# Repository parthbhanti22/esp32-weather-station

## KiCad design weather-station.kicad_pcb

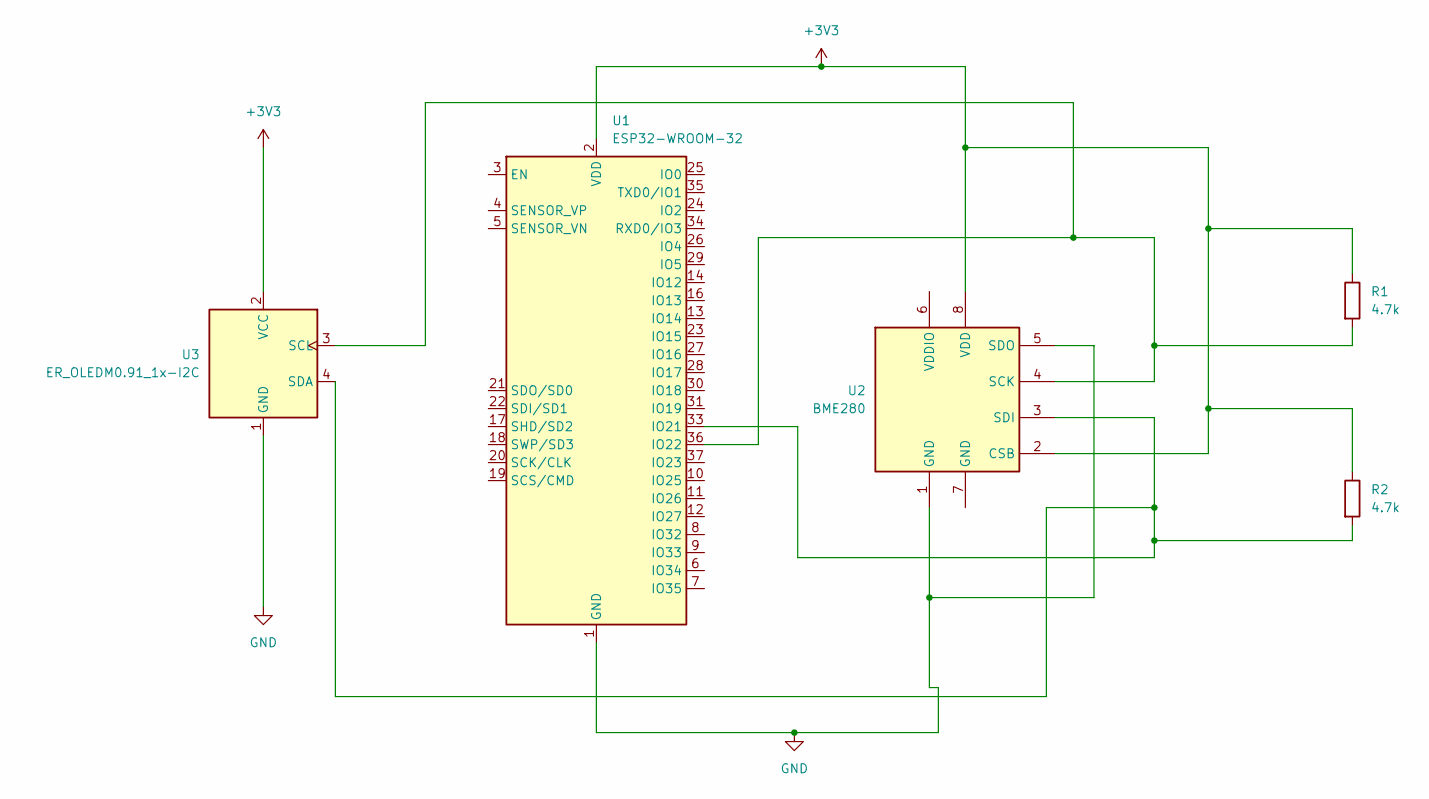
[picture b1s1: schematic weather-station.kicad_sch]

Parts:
R1, R2: 4.7k; R_1206_3216Metric_Pad1.30x1.75mm_HandSolder
U1: ESP32-WROOM-32
U2: BME280; Bosch_LGA-8_2.5x2.5mm_P0.65mm_ClockwisePinNumbering
U3: ER_OLEDM0.91_1x-I2C

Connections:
+3V3: R1.1, R2.1, U1.2 (VDD), U2.2 (CSB), U2.8 (VDD), U3.2 (VCC)
GND: U1.1 (GND), U1.15 (GND), U1.38 (GND), U1.39 (GND), U2.1 (GND), U2.5 (SDO), U3.1 (GND)
unnamed: R2.2, U1.33 (IO21), U2.3 (SDI), U3.4 (SDA)
unnamed: R1.2, U1.36 (IO22), U2.4 (SCK), U3.3 (SCL)

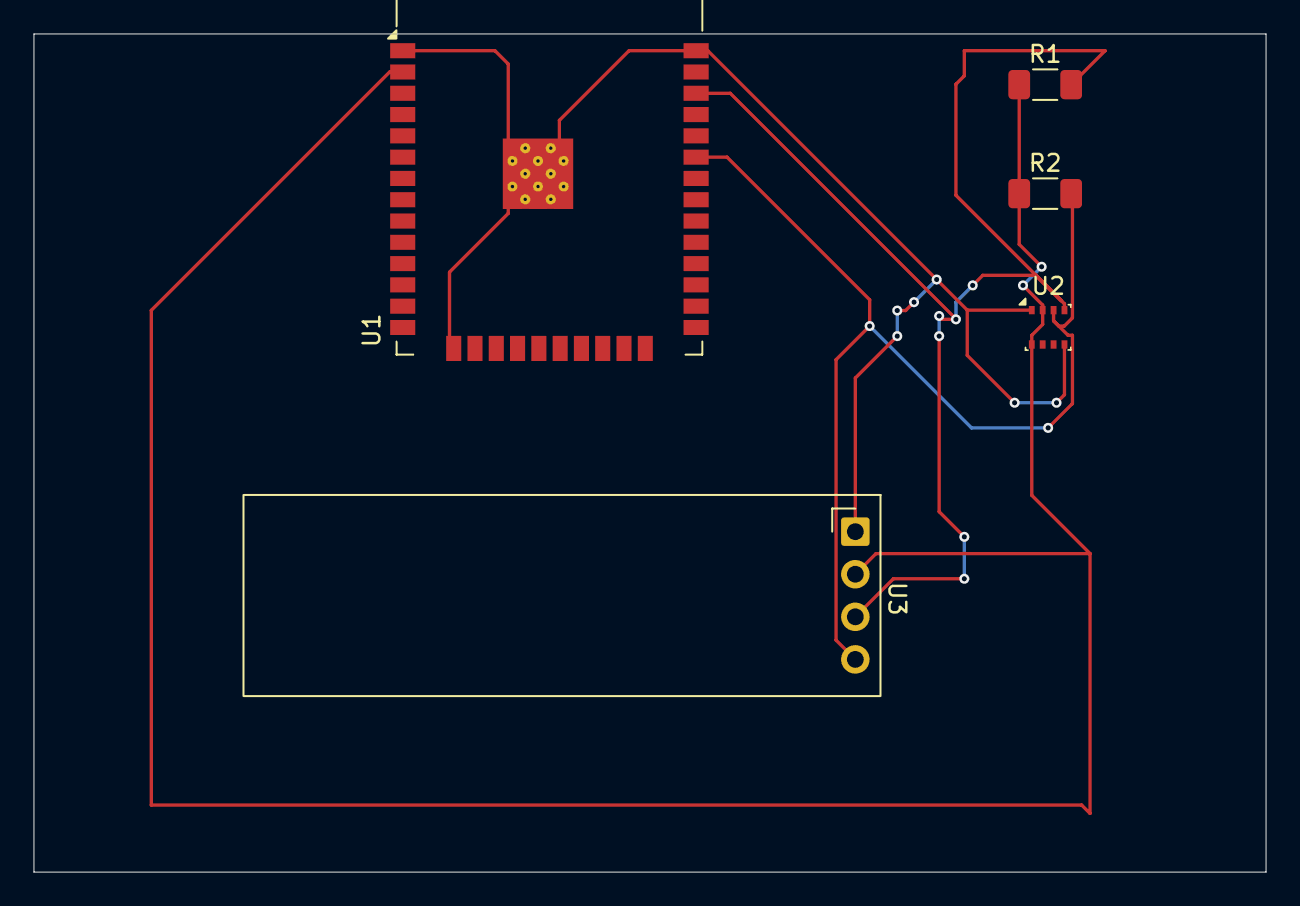
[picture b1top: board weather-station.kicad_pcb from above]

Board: 2 copper layers, 73.5 x 50.0 mm, 5 parts (0 on the bottom side), 4 nets.
